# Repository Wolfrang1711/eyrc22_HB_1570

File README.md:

# eYantra-HB_1570

Our Holonomic Drive Theme Project is a cutting-edge endeavor developed for the prestigious E-Yantra Robotics Competition '23. The core objective of this project is to conceive, construct, and program a holonomic drive robot. This robot is engineered to not only accomplish intricate tasks but also create elaborate and captivating art.
With a holistic approach that combines mechanical engineering, advanced software programming, and artistic creativity, our project represents the convergence of technology and artistry. Through this endeavor, we aim to showcase the limitless potential of holonomic drive systems in robotics and push the boundaries of what robots can achieve in terms of precision, agility, and artistic expression.

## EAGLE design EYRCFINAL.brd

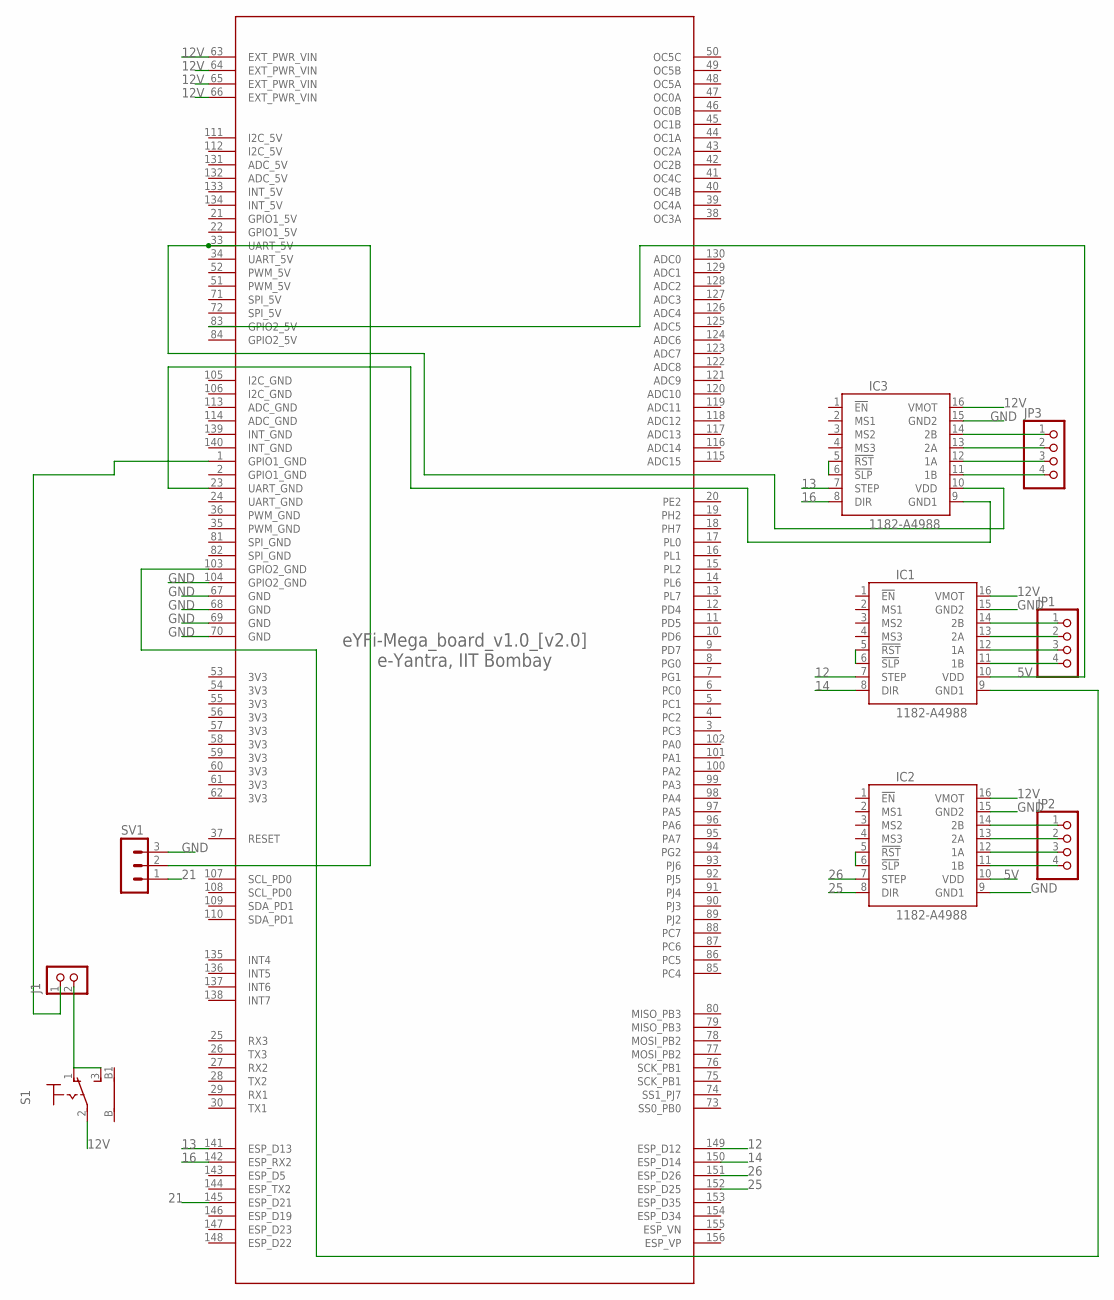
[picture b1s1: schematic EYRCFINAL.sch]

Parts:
IC1, IC2, IC3: 1182-A4988; A4988
J1: CON_TERMINAL_BLOCK_02-5MM; TERMINAL_BLOCK_2P_5
JP1, JP2, JP3: PINHD-1X4; 1X04
S1: 9070-1W
SV1: MA03-1
U$1: EYFI-MEGA_V2.0

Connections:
3V3: U$1.53 (3V3), U$1.54 (3V3), U$1.55 (3V3), U$1.56 (3V3), U$1.57 (3V3), U$1.58 (3V3), U$1.59 (3V3), U$1.60 (3V3), U$1.61 (3V3), U$1.62 (3V3)
5V: IC1.10 (VDD), IC2.10 (VDD), U$1.83 (GPIO2_5V)
12: IC1.7 (STEP), U$1.149 (ESP_D12)
12V: IC1.16 (VMOT), IC2.16 (VMOT), IC3.16 (VMOT), S1.2, U$1.63 (EXT_PWR_VIN), U$1.64 (EXT_PWR_VIN), U$1.65 (EXT_PWR_VIN), U$1.66 (EXT_PWR_VIN)
13: IC3.7 (STEP), U$1.141 (ESP_D13)
14: IC1.8 (DIR), U$1.150 (ESP_D14)
16: IC3.8 (DIR), U$1.142 (ESP_RX2)
21: SV1.1, U$1.145 (ESP_D21)
25: IC2.8 (DIR), U$1.152 (ESP_D25)
26: IC2.7 (STEP), U$1.151 (ESP_D26)
ADC_5V: U$1.131 (ADC_5V), U$1.132 (ADC_5V)
ADC_GND: U$1.113 (ADC_GND), U$1.114 (ADC_GND)
GND: IC1.9 (GND1), IC1.15 (GND2), IC2.9 (GND1), IC2.15 (GND2), IC3.9 (GND1), IC3.15 (GND2), SV1.3, U$1.23 (UART_GND), U$1.67 (GND), U$1.68 (GND), U$1.69 (GND), U$1.70 (GND), U$1.103 (GPIO2_GND), U$1.104 (GPIO2_GND)
GPIO1_5V: U$1.21 (GPIO1_5V), U$1.22 (GPIO1_5V)
GPIO1_GND: U$1.2 (GPIO1_GND)
GPIO2_5V: U$1.84 (GPIO2_5V)
I2C_5V: U$1.111 (I2C_5V), U$1.112 (I2C_5V)
I2C_GND: U$1.105 (I2C_GND), U$1.106 (I2C_GND)
INT_5V: U$1.133 (INT_5V), U$1.134 (INT_5V)
INT_GND: U$1.139 (INT_GND), U$1.140 (INT_GND)
unnamed: IC1.14 (2B), JP1.1
unnamed: IC1.13 (2A), JP1.2
unnamed: IC1.12 (1A), JP1.3
unnamed: IC1.11 (1B), JP1.4
unnamed: IC2.14 (2B), JP2.1
unnamed: IC2.13 (2A), JP2.2
unnamed: IC2.12 (1A), JP2.3
unnamed: IC2.11 (1B), JP2.4
unnamed: IC3.14 (2B), JP3.1
unnamed: IC3.13 (2A), JP3.2
unnamed: IC3.12 (1A), JP3.3
unnamed: IC3.11 (1B), JP3.4
unnamed: J1.1, U$1.1 (GPIO1_GND)
unnamed: IC3.10 (VDD), SV1.2, U$1.33 (UART_5V)
unnamed: J1.2, S1.1 (O), S1.3 (S)
unnamed: IC3.5 (!RST), IC3.6 (!SLP)
unnamed: IC1.5 (!RST), IC1.6 (!SLP)
unnamed: IC2.5 (!RST), IC2.6 (!SLP)
PWM_5V: U$1.51 (PWM_5V), U$1.52 (PWM_5V)
PWM_GND: U$1.35 (PWM_GND), U$1.36 (PWM_GND)
SPI_5V: U$1.71 (SPI_5V), U$1.72 (SPI_5V)
SPI_GND: U$1.81 (SPI_GND), U$1.82 (SPI_GND)
UART_5V: U$1.34 (UART_5V)
UART_GND: U$1.24 (UART_GND)

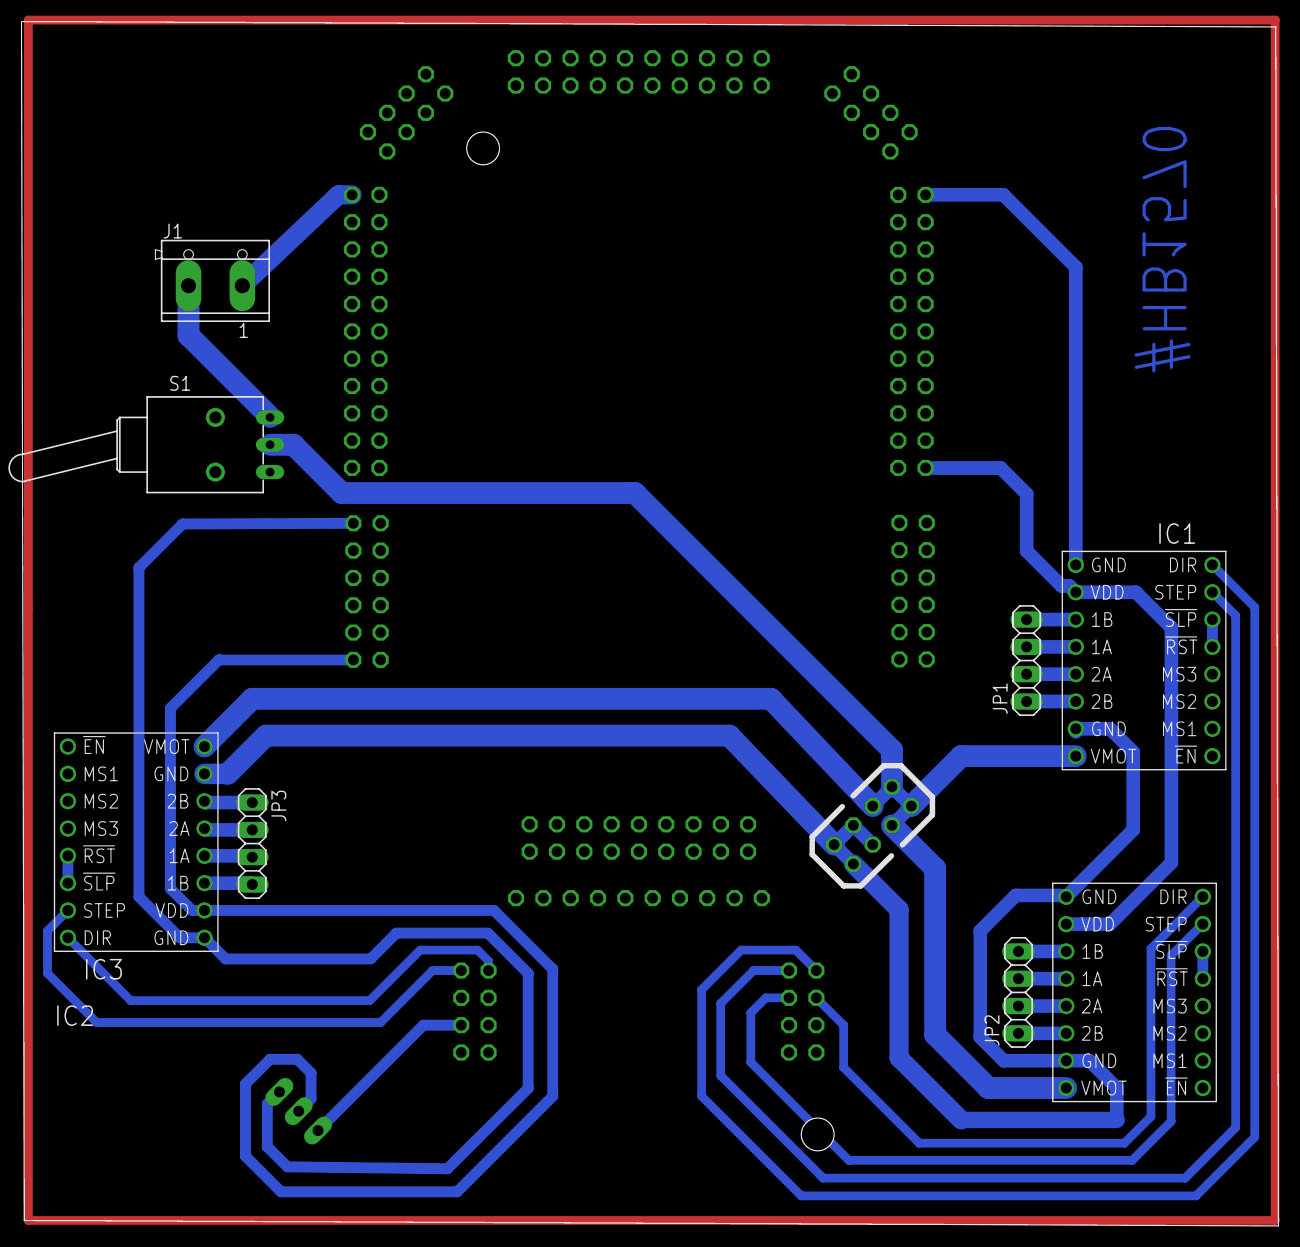
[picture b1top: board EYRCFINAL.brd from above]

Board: 2 copper layers, 116.9 x 112.0 mm, 10 parts (1 on the bottom side), 40 nets.

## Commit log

2022-10-27 updated controller to class
2022-10-27 Rebasing Files
2022-10-30 feedback, controller updated
2022-11-02 Updated Task 2
2022-11-02 updating
2023-02-07 Task 3 Submission
2023-02-08 task4 added task5 initialised
2023-02-08 Rebased
2023-02-08 camera calibration
2023-02-08 task 5
2023-02-11 wireless comm added
2023-02-11 wireless done
2023-02-12 hello
2023-02-12 motors working
2023-02-13 teleop done and dusted
2023-02-18 goal to goal in progress
2023-02-20 task5A done and dusted
2023-03-02 function mode added
2023-03-28 updated repo
2023-03-28 rearrange
